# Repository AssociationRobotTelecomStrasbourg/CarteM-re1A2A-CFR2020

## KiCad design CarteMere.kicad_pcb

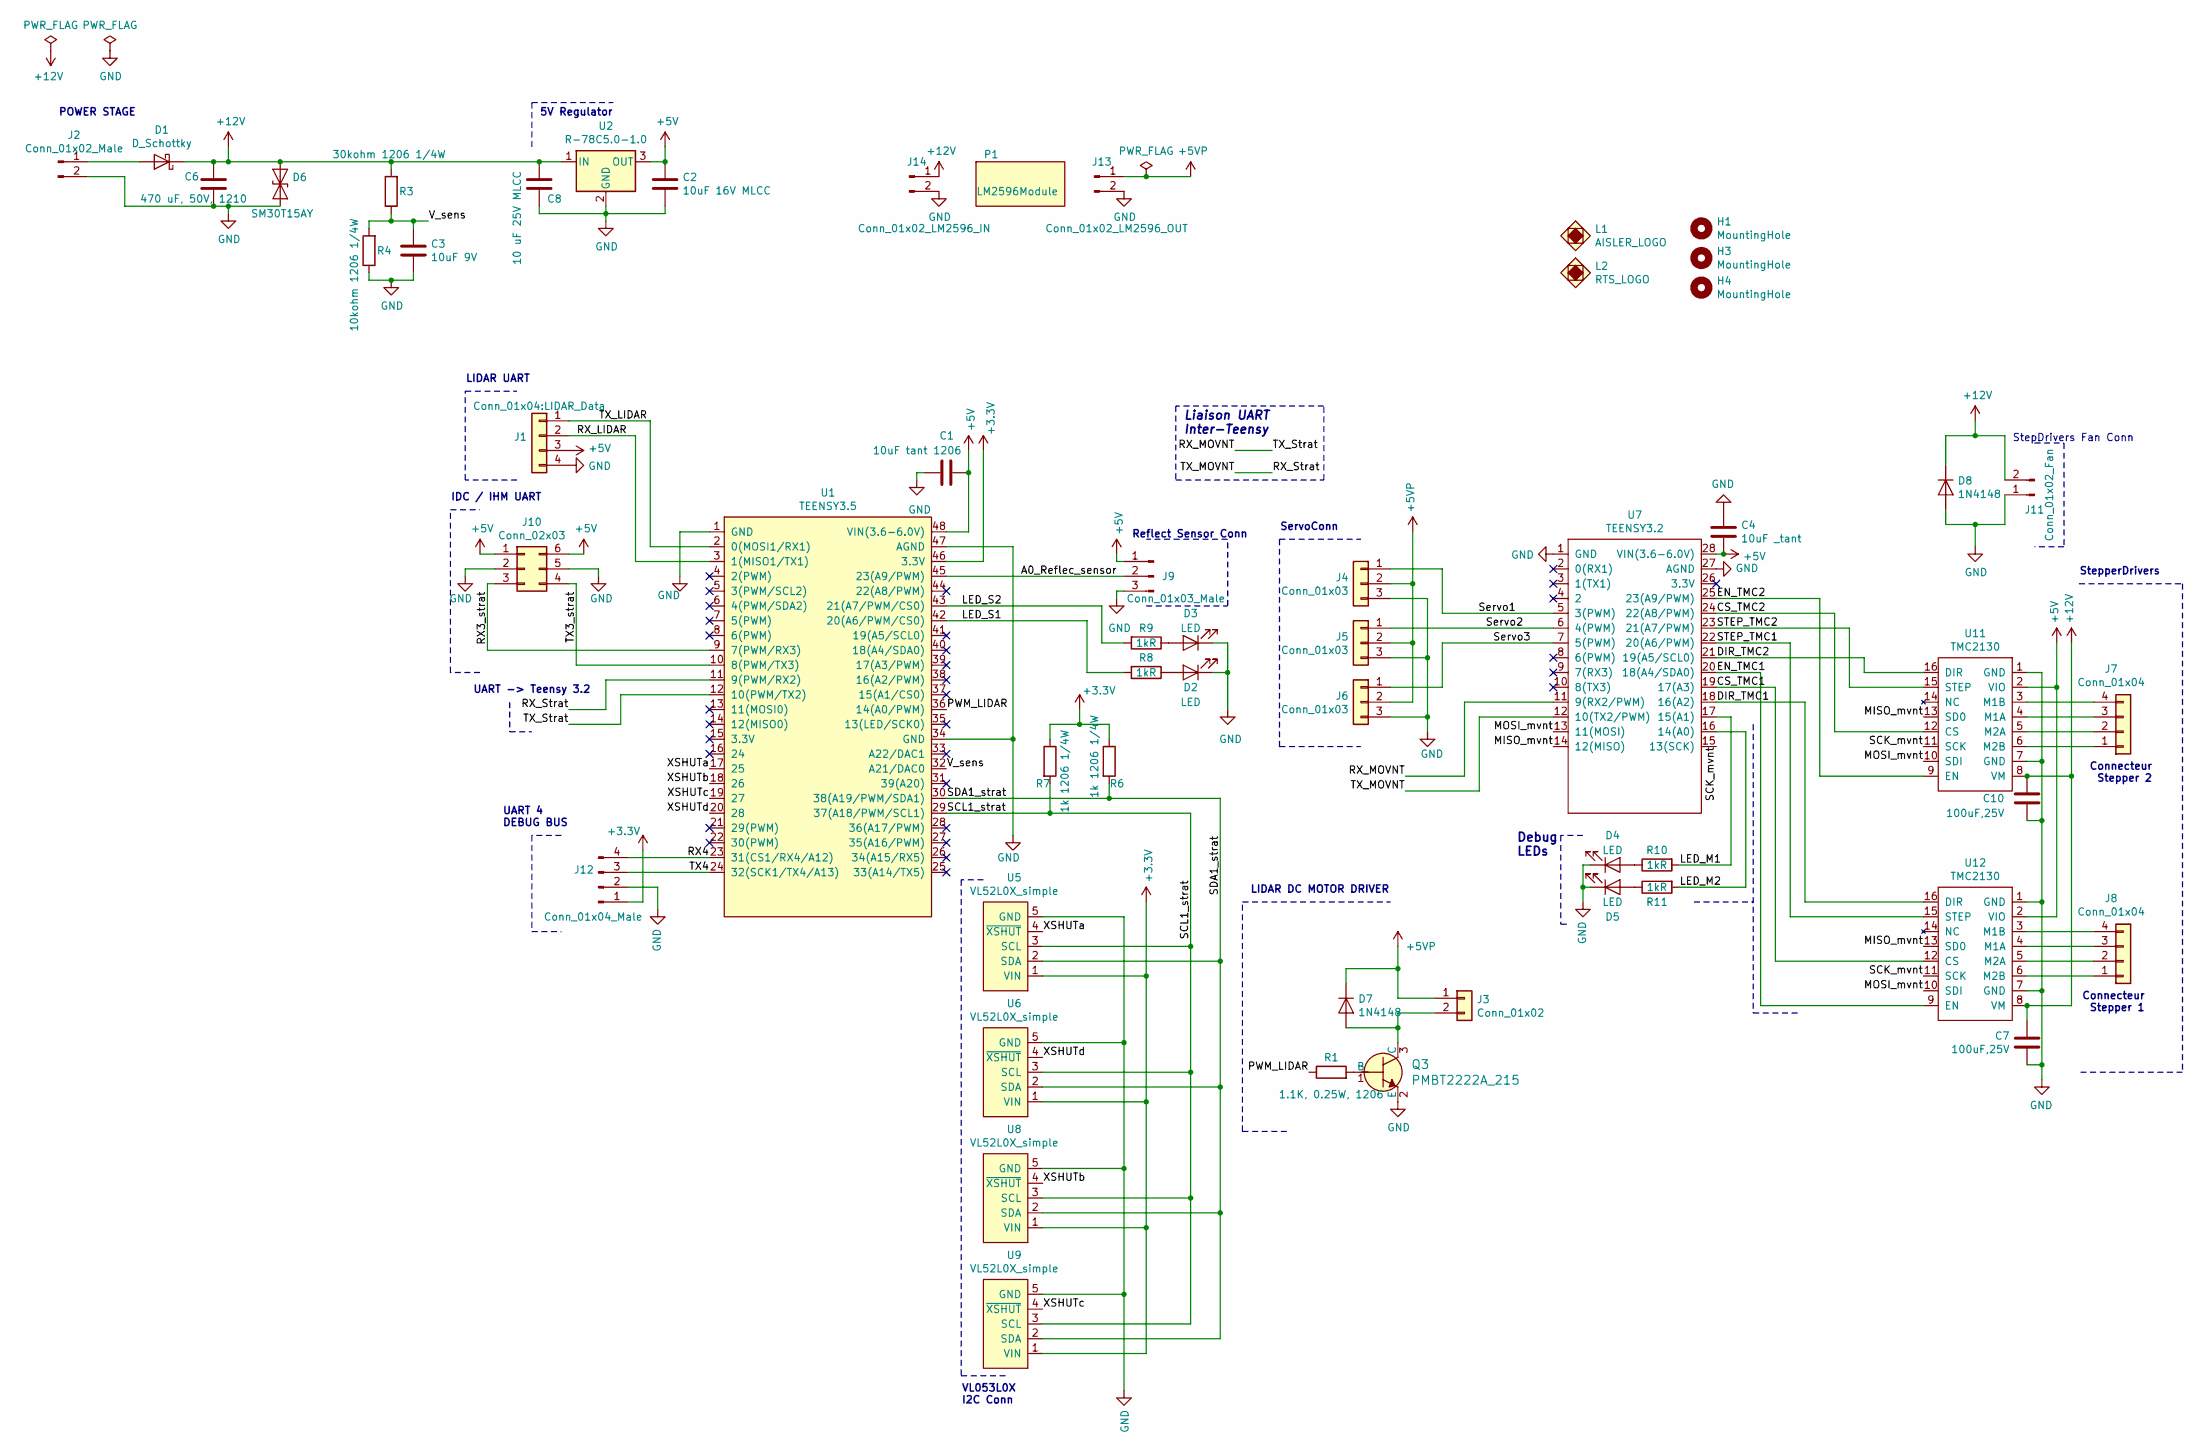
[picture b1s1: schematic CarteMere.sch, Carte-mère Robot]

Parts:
C1: 10uF tant 1206; C_1206_3216Metric_Pad1.42x1.75mm_HandSolder
C2: 10uF 16V MLCC; C_1206_3216Metric_Pad1.42x1.75mm_HandSolder
C3: 10uF 9V; C_1206_3216Metric_Pad1.42x1.75mm_HandSolder
C4: 10uF _tant; C_1206_3216Metric_Pad1.42x1.75mm_HandSolder
C6: 470 uF, 50V, 1210; C_1210_3225Metric_Pad1.42x2.65mm_HandSolder
C7, C10: 100uF,25V; CP_Radial_D6.3mm_P2.50mm
C8: 10 uF 25V MLCC; C_1206_3216Metric_Pad1.42x1.75mm_HandSolder
D1: D_Schottky; D_SMA_Handsoldering
D2, D3, D4, D5: LED; LED_1206_3216Metric_Pad1.42x1.75mm_HandSolder
D6: SM30T15AY; D_SMC_Handsoldering
D7, D8: 1N4148; D_SOD-123
H1, H3, H4: MountingHole; MountingHole_3.2mm_M3
J1: Conn_01x04:LIDAR_Data; JST_PH_B4B-PH-K_1x04_P2.00mm_Vertical
J2: Conn_01x02_Male; OSTOQ027151
J3: Conn_01x02; JST_PH_B2B-PH-K_1x02_P2.00mm_Vertical
J4, J5, J6: Conn_01x03; PinHeader_1x03_P2.54mm_Vertical
J7, J8: Conn_01x04; JST_XH_B4B-XH-A_1x04_P2.50mm_Vertical
J9: Conn_01x03_Male; PinSocket_1x03_P2.54mm_Vertical
J10: Conn_02x03; IDC-Header_2x03_P2.54mm_Vertical
J11: Conn_01x02_Fan; JST_XH_B2B-XH-A_1x02_P2.50mm_Vertical
J12: Conn_01x04_Male; JST_XH_B4B-XH-AM_1x04_P2.50mm_Vertical
J13: Conn_01x02_LM2596_OUT; BatConn
J14: Conn_01x02_LM2596_IN; BatConn
L1: AISLER_LOGO; aisler
L2: RTS_LOGO; rts
P1: LM2596Module; LM2596 Module
Q3: PMBT2222A_215; SOT-23_DGS_Handsoldering; MPN PMBT2222A,215; Digi-Key_PN 1727-2956-1-ND
R1: 1.1K, 0.25W, 1206; R_1206_3216Metric_Pad1.42x1.75mm_HandSolder
R3: 30kohm 1206 1/4W; R_1206_3216Metric_Pad1.42x1.75mm_HandSolder
R4: 10kohm 1206 1/4W; R_1206_3216Metric_Pad1.42x1.75mm_HandSolder
R6, R7: 1k 1206 1/4W; R_1206_3216Metric_Pad1.42x1.75mm_HandSolder
R8, R9, R10, R11: 1kR; R_1206_3216Metric_Pad1.42x1.75mm_HandSolder
U1: TEENSY3.5; Teensy3.6_RTS
U2: R-78C5.0-1.0; Converter_DCDC_RECOM_R-78E-0.5_THT
U5, U6, U8, U9: VL52L0X_simple; JST_XH_B5B-XH-A_1x05_P2.50mm_Vertical
U7: TEENSY3.2; TEENSY3.2_RTS
U11, U12: TMC2130; TMC2130_breakout

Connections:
+3V3: J12.1, R6.1, R7.1, U1.46 (3.3V), U5.1 (VIN), U6.1 (VIN), U8.1 (VIN), U9.1 (VIN)
+5V: C1.1, C2.1, C4.2, J1.3, J9.1, J10.1, J10.6, U1.48 (VIN(3.6-6.0V)), U2.3 (OUT), U7.28 (VIN(3.6-6.0V)), U11.2 (VIO), U12.2 (VIO)
+5VP: D7.1 (K), J3.1, J4.2, J5.2, J6.2, J13.1
+12V: C6.1, C7.1, C8.1, C10.1, D1.1 (K), D6.1 (A1), D8.1 (K), J11.2, J14.1, R3.2, U2.1 (IN), U11.8 (VM), U12.8 (VM)
/A0_Reflec_sensor: J9.2, U1.45 (23(A9/PWM))
/CS_TMC1: U7.19 (17(A3)), U12.12 (CS)
/CS_TMC2: U7.24 (22(A8/PWM)), U11.12 (CS)
/DIR_TMC1: U7.18 (16(A2)), U12.16 (DIR)
/DIR_TMC2: U7.21 (19(A5/SCL0)), U11.16 (DIR)
/EN_TMC1: U7.20 (18(A4/SDA0)), U12.9 (EN)
/EN_TMC2: U7.25 (23(A9/PWM)), U11.9 (EN)
/LED_M1: R10.2, U7.17 (15(A1))
/LED_M2: R11.2, U7.16 (14(A0))
/LED_S1: R8.2, U1.42 (20(A6/PWM/CS0))
/LED_S2: R9.2, U1.43 (21(A7/PWM/CS0))
/MISO_mvnt: U7.14 (12(MISO)), U11.13 (SD0), U12.13 (SD0)
/MOSI_mvnt: U7.13 (11(MOSI)), U11.10 (SDI), U12.10 (SDI)
/PWM_LIDAR: R1.1, U1.36 (14(A0/PWM))
/RX3_strat: J10.3, U1.9 (7(PWM/RX3))
/RX4: J12.4, U1.23 (31(CS1/RX4/A12))
/RX_LIDAR: J1.2, U1.3 (1(MISO1/TX1))
/RX_MOVNT: U1.12 (10(PWM/TX2)), U7.11 (9(RX2/PWM))
/RX_Strat: U1.11 (9(PWM/RX2)), U7.12 (10(TX2/PWM))
/SCK_mvnt: U7.15 (13(SCK)), U11.11 (SCK), U12.11 (SCK)
/SCL1_strat: R7.2, U1.29 (37(A18/PWM/SCL1)), U5.3 (SCL), U6.3 (SCL), U8.3 (SCL), U9.3 (SCL)
/SDA1_strat: R6.2, U1.30 (38(A19/PWM/SDA1)), U5.2 (SDA), U6.2 (SDA), U8.2 (SDA), U9.2 (SDA)
/STEP_TMC1: U7.22 (20(A6/PWM)), U12.15 (STEP)
/STEP_TMC2: U7.23 (21(A7/PWM)), U11.15 (STEP)
/Servo1: J4.1, U7.5 (3(PWM))
/Servo2: J5.1, U7.6 (4(PWM))
/Servo3: J6.1, U7.7 (5(PWM))
/TX3_strat: J10.4, U1.10 (8(PWM/TX3))
/TX4: J12.3, U1.24 (32(SCK1/TX4/A13))
/TX_LIDAR: J1.1, U1.2 (0(MOSI1/RX1))
/V_sens: C3.1, R3.1, R4.2, U1.32 (A21/DAC0)
/XSHUTa: U1.17 (25), U5.4 (~XSHUT)
/XSHUTb: U1.18 (26), U8.4 (~XSHUT)
/XSHUTc: U1.19 (27), U9.4 (~XSHUT)
/XSHUTd: U1.20 (28), U6.4 (~XSHUT)
GND: C1.2, C2.2, C3.2, C4.1, C6.2, C7.2, C8.2, C10.2, D2.1 (K), D3.1 (K), D4.1 (K), D5.1 (K), D6.2 (A2), D8.2 (A), J1.4, J2.2, J4.3, J5.3, J6.3, J9.3, J10.2, J10.5, J11.1, J12.2, J13.2, J14.2, Q3.2 (E), R4.1, U1.1 (GND), U1.34 (GND), U1.47 (AGND), U2.2 (GND), U5.5 (GND), U6.5 (GND), U7.1 (GND), U7.27 (AGND), U8.5 (GND), U9.5 (GND), U11.1 (GND), U11.7 (GND), U12.1 (GND), U12.7 (GND)
unnamed: D1.2 (A), J2.1
unnamed: D2.2 (A), R8.1
unnamed: D3.2 (A), R9.1
unnamed: D4.2 (A), R10.1
unnamed: D5.2 (A), R11.1
unnamed: D7.2 (A), J3.2, Q3.3 (C)
unnamed: J7.1, U11.6 (M2B)
unnamed: J7.2, U11.5 (M2A)
unnamed: J7.3, U11.4 (M1A)
unnamed: J7.4, U11.3 (M1B)
unnamed: J8.1, U12.6 (M2B)
unnamed: J8.2, U12.5 (M2A)
unnamed: J8.3, U12.4 (M1A)
unnamed: J8.4, U12.3 (M1B)
unnamed: Q3.1 (B), R1.2

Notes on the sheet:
Connecteur Stepper 1
Liaison UART Inter-Teensy
Connecteur Stepper 2
StepDrivers Fan Conn
IDC / IHM UART
ServoConn
StepperDrivers
VL053L0X I2C Conn
Debug LEDs
LIDAR DC MOTOR DRIVER
UART 4 DEBUG BUS
UART -> Teensy 3.2
LIDAR UART
Reflect Sensor Conn
POWER STAGE
5V Regulator

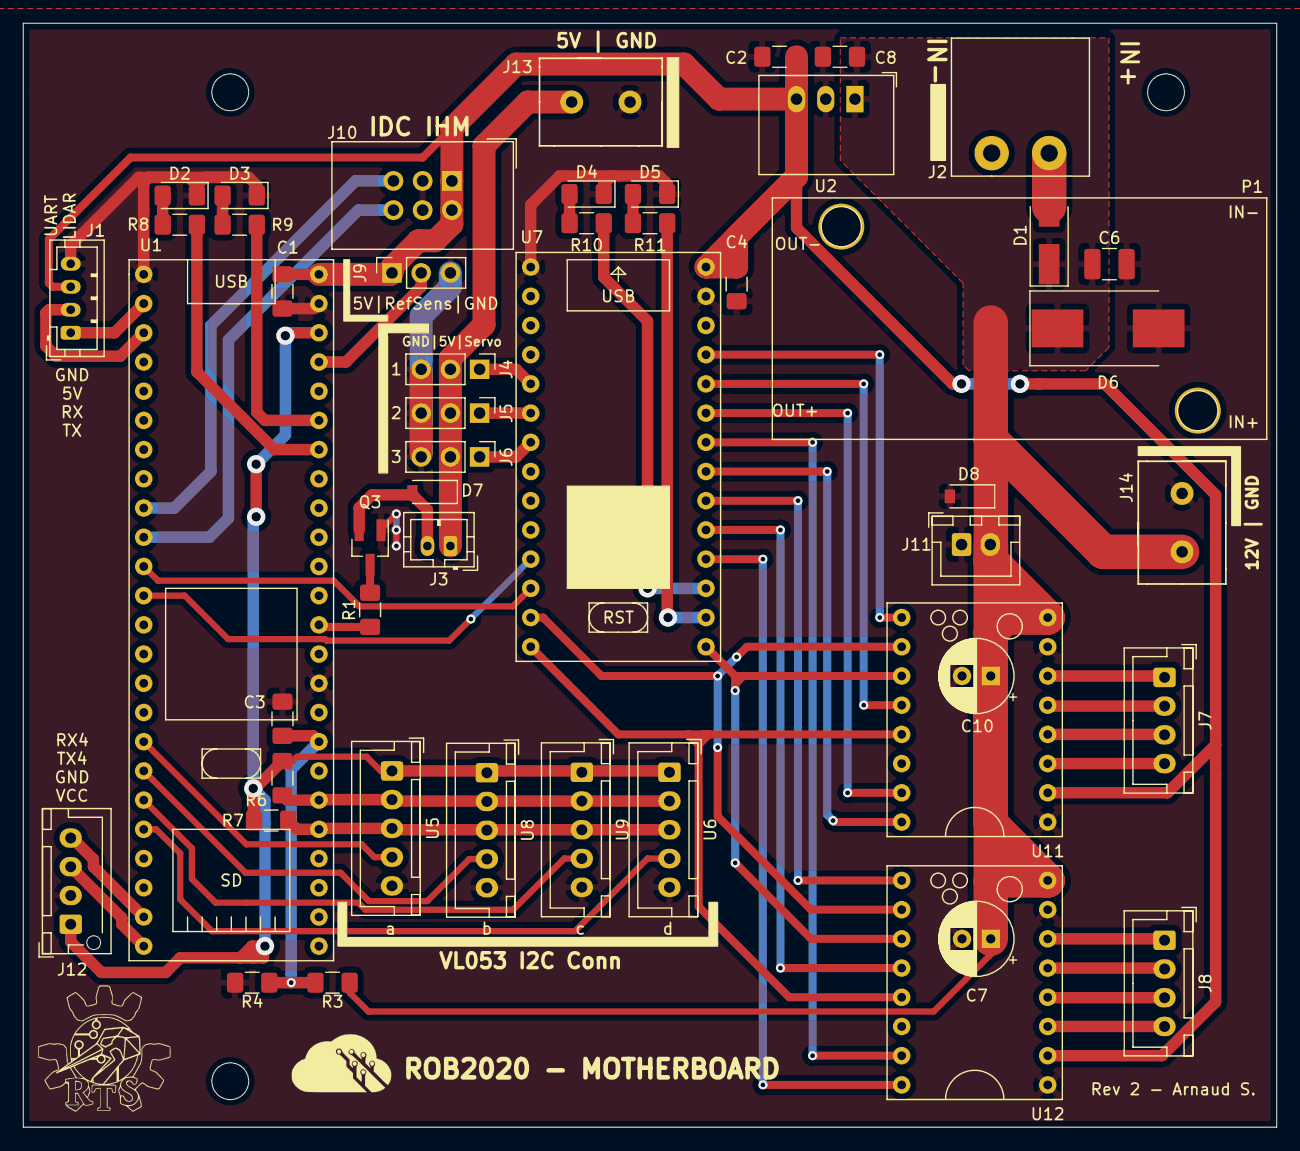
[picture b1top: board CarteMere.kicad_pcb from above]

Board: 2 copper layers, 109.0 x 96.0 mm, 55 parts (0 on the bottom side), 55 nets.

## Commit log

2020-02-26 Version 0.9
2020-02-27 Mise à jour
2020-06-20 Nettoyage du schéma, ajout de l'UART 4 sur Teensy 3.6 pour debug, renforcement alimentation 5V
